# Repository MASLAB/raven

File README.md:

# raven
Robot Hardware Controller

## Pcb
Color pallet works best with KiCad wDark theme

## Firmware
Built using cmake and all dependencies exist locally

Install build tools if you need to
```
sudo apt install ninja-build cmake gcc-arm-none-eabi
```

### Compiling
Compile from motor-hub folder
```
cmake . --preset=Release
cd Release
ninja
```

### Linker Bug
For some reason, STM32CubeMX has a bug in generating the linker script, and misses RAM in a few places

Ignore the project generated linker file, as I changed the CMakeLists.txt to link to the one in firmware folder

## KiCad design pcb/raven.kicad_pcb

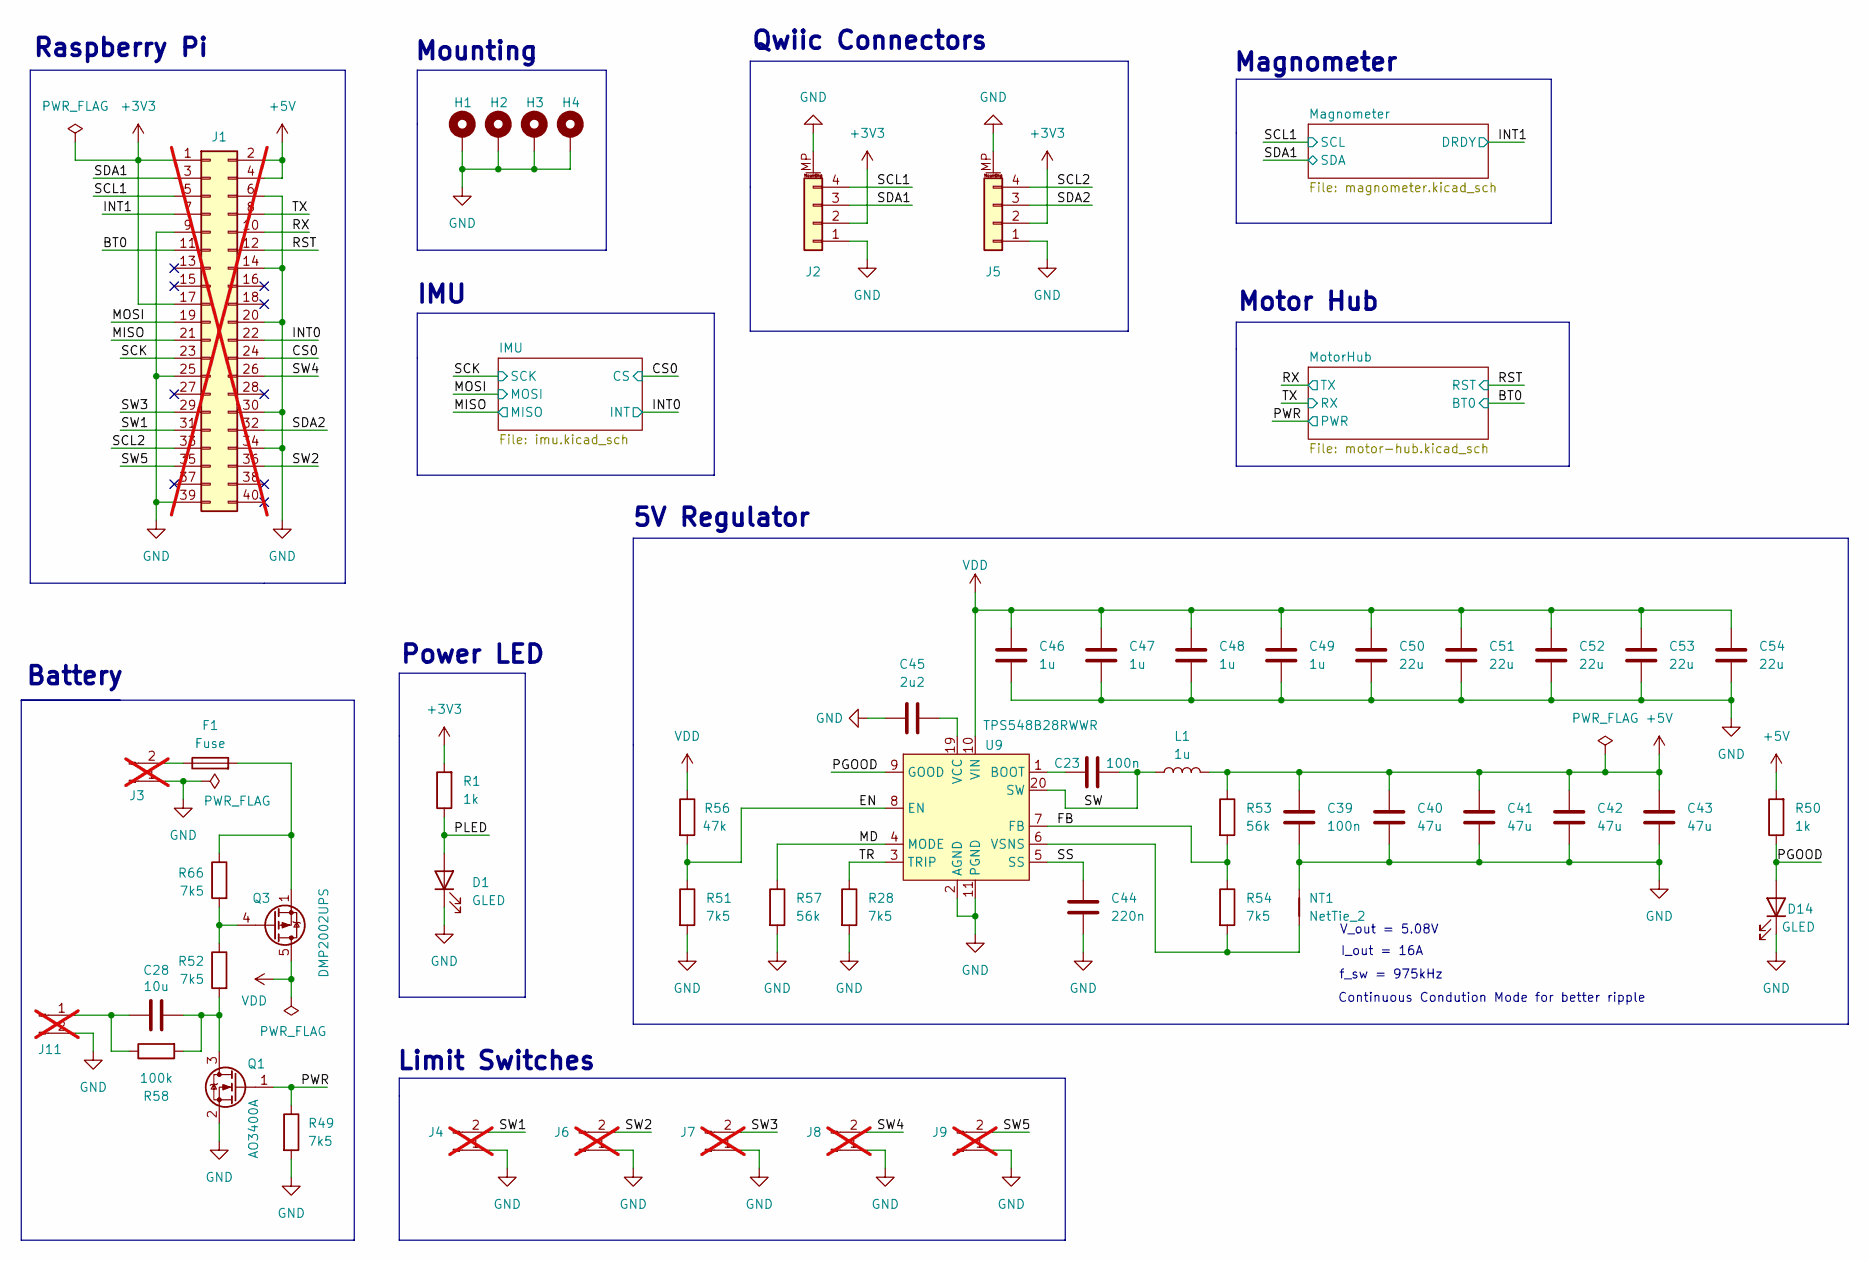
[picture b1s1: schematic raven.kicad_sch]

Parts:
C23: 100n; C_0603_1608Metric; LCSC C14663
C28: 10u; C_0603_1608Metric; LCSC C96446
C39: 100n; C_0402_1005Metric; LCSC C1525
C40, C41, C42, C43: 47u; C_1206_3216Metric; LCSC C96123
C44: 220n; C_0402_1005Metric; LCSC C16772
C45: 2u2; C_0805_2012Metric; LCSC C377773
C46, C47, C48, C49: 1u; C_0402_1005Metric; LCSC C52923
C50, C51, C52, C53, C54: 22u; C_0805_2012Metric; LCSC C45783
D1, D14: GLED; LED_0603_1608Metric; LCSC C72043
F1: Fuse; Fuse_1206_3216Metric; LCSC C2838917
H1, H2, H3, H4: MountingHole_Pad; MountingHole_2.5mm_Pad
J1: Conn_02x20_Odd_Even; PinSocket_2x20_P2.54mm_Vertical; LCSC C35165; not fitted
J2, J5: Conn_01x04_MountingPin; JST_SH_SM04B-SRSS-TB_1x04-1MP_P1.00mm_Horizontal; LCSC C160404
J3: Conn_01x02_Pin; AMASS_XT30UPB-M_1x02_P5.0mm_Vertical; LCSC C428721; not fitted
J4, J6, J7, J8, J9: Conn_01x02_Pin; PinHeader_1x02_P2.54mm_Vertical; LCSC C492401; not fitted
J11: Conn_01x02_Pin; JST_PH_B2B-PH-K_1x02_P2.00mm_Vertical; LCSC C131337; not fitted
L1: 1u; L_0660A; LCSC C18199443
NT1: NetTie_2; NetTie-2_SMD_Pad0.5mm
Q1: AO3400A; SOT-23; LCSC C20917
Q3: DMP2002UPS; LCSC C154869
R1, R50: 1k; R_0402_1005Metric; LCSC C11702
R28, R49, R51, R52, R54, R66: 7k5; R_0402_1005Metric; LCSC C25918
R53, R57: 56k; R_0402_1005Metric; LCSC C25796
R56: 47k; R_0402_1005Metric; LCSC C25792
R58: 100k; R_0402_1005Metric; LCSC C25741
U9: TPS548B28RWWR; LCSC C3188716

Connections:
+3V3: J1.1, J1.17, J2.2, J5.2, R1.2; also elsewhere on the board
+5V: C39.2, C40.1, C41.1, C42.1, C43.1, J1.2, J1.4, L1.2, R50.2, R53.1; also elsewhere on the board
/BT0: J1.11; also elsewhere on the board
/CS0: J1.24; also elsewhere on the board
/EN: R51.1, R56.2, U9.8 (EN)
/FB: R53.2, R54.1, U9.7 (FB)
/INT0: J1.22; also elsewhere on the board
/INT1: J1.7; also elsewhere on the board
/MD: R57.1, U9.4 (MODE)
/MISO: J1.21; also elsewhere on the board
/MOSI: J1.19; also elsewhere on the board
/PGOOD: D14.2 (A), R50.1, U9.9 (GOOD)
/PLED: D1.2 (A), R1.1
/PWR: Q1.1 (G), R49.1; also elsewhere on the board
/RST: J1.12; also elsewhere on the board
/RX: J1.10; also elsewhere on the board
/SCK: J1.23; also elsewhere on the board
/SCL1: J1.5, J2.4; also elsewhere on the board
/SCL2: J1.33, J5.4
/SDA1: J1.3, J2.3; also elsewhere on the board
/SDA2: J1.32, J5.3
/SS: C44.1, U9.5 (SS)
/SW: C23.2, L1.1, U9.20 (SW)
/SW1: J1.31, J4.2
/SW2: J1.36, J6.2
/SW3: J1.29, J7.2
/SW4: J1.26, J8.2
/SW5: J1.35, J9.2
/TR: R28.1, U9.3 (TRIP)
/TX: J1.8; also elsewhere on the board
GND: C39.1, C40.2, C41.2, C42.2, C43.2, C44.2, C45.1, C46.2, C47.2, C48.2, C49.2, C50.2, C51.2, C52.2, C53.2, C54.2, D1.1 (K), D14.1 (K), H1.1, H2.1, H3.1, H4.1, J1.6, J1.9, J1.14, J1.20, J1.25, J1.30, J1.34, J1.39, J2.1, J2.MP (MountPin), J3.1, J4.1, J5.1, J5.MP (MountPin), J6.1, J7.1, J8.1, J9.1, J11.2, NT1.1, Q1.2 (S), R28.2, R49.2, R51.2, R57.2, U9.2 (AGND), U9.11 (PGND), U9.12 (PGND), U9.13 (PGND), U9.14 (PGND), U9.15 (PGND), U9.16 (PGND), U9.17 (PGND), U9.18 (PGND); also elsewhere on the board
unnamed: F1.2, Q3.1 (S), Q3.2 (S), Q3.3 (S), R66.1
unnamed: F1.1, J3.2
unnamed: C28.1, J11.1, R58.1
unnamed: C28.2, Q1.3 (D), R52.2, R58.2
unnamed: Q3.4 (G), R52.1, R66.2
unnamed: C23.1, U9.1 (BOOT)
unnamed: C45.2, U9.19 (VCC)
unnamed: NT1.2, R54.2, U9.6 (VSNS)
VDD: C46.1, C47.1, C48.1, C49.1, C50.1, C51.1, C52.1, C53.1, C54.1, Q3.5 (D), Q3.6 (D), Q3.7 (D), Q3.8 (D), R56.1, U9.10 (VIN), U9.21 (VIN); also elsewhere on the board

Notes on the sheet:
Mounting
Power LED
5V Regulator
IMU
Motor Hub
V_out = 5.08V
Limit Switches
Continuous Condution Mode for better ripple
Qwiic Connectors
Battery
I_out = 16A
f_sw = 975kHz
Raspberry Pi
Magnometer

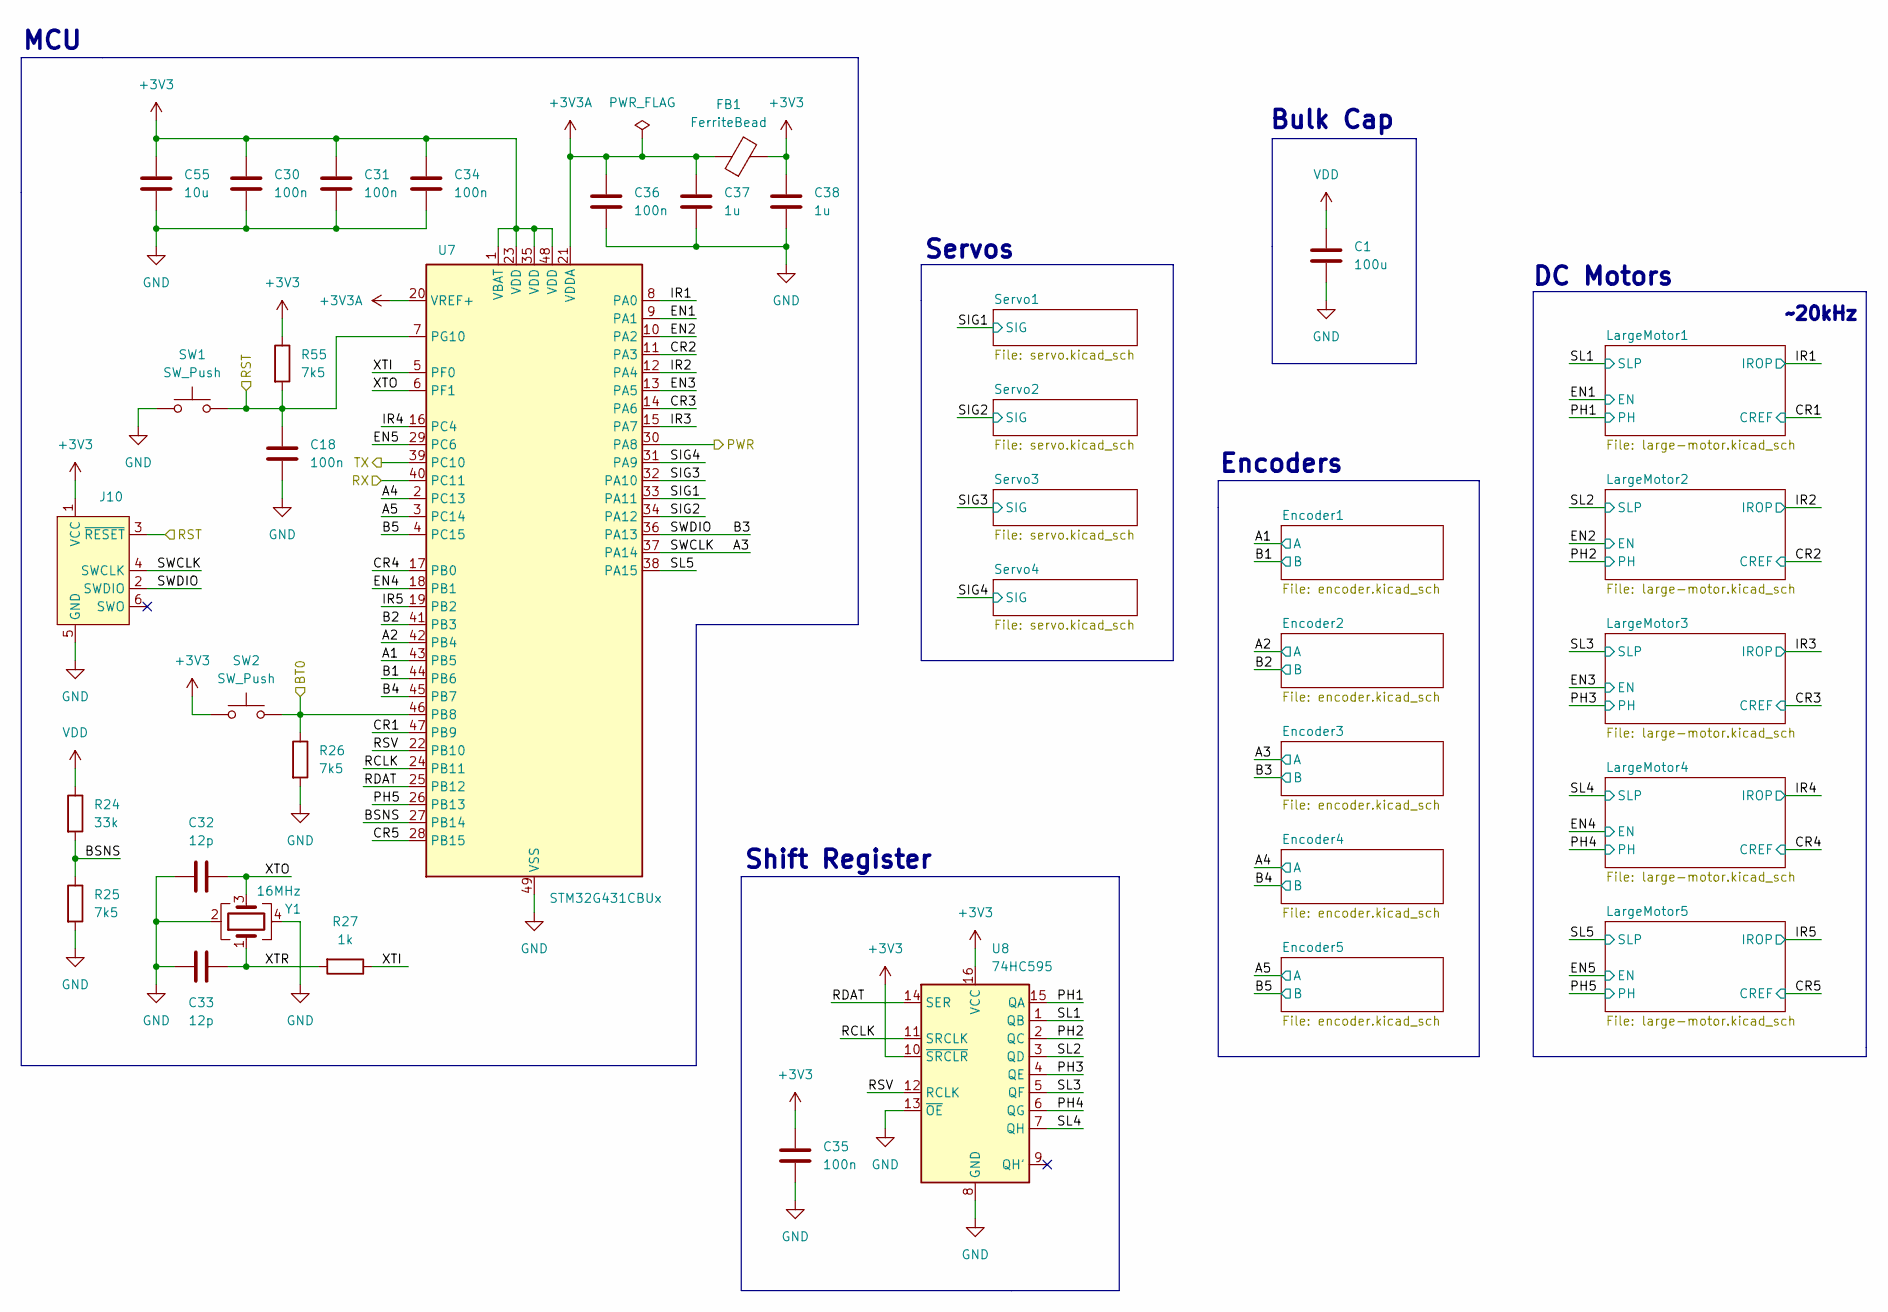
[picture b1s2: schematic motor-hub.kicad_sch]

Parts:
C1: 100u; C_Elec_8x6.2; LCSC C178539
C18, C30, C31, C34, C35, C36: 100n; C_0402_1005Metric; LCSC C1525
C32, C33: 12p; C_0402_1005Metric; LCSC C1547
C37, C38: 1u; C_0402_1005Metric; LCSC C52923
C55: 10u; C_0402_1005Metric; LCSC C15525
FB1: FerriteBead; L_0805_2012Metric; LCSC C1017
J10: Conn_ARM_SWD_TagConnect_TC2030-NL; Tag-Connect_TC2030-IDC-NL_2x03_P1.27mm_Vertical
R24: 33k; R_0402_1005Metric; LCSC C25779
R25, R26, R55: 7k5; R_0402_1005Metric; LCSC C25918
R27: 1k; R_0402_1005Metric; LCSC C11702
SW1, SW2: SW_Push; TS-1088; LCSC C720477
U7: STM32G431CBUx; QFN-48-1EP_7x7mm_P0.5mm_EP5.6x5.6mm; LCSC C529356
U8: 74HC595; SOIC-16_3.9x9.9mm_P1.27mm; LCSC C5947
Y1: 16MHz; Crystal_SMD_3225-4Pin_3.2x2.5mm; LCSC C13738

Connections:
+3V3: C30.1, C31.1, C34.1, C35.1, C38.1, C55.1, FB1.2, J10.1 (VCC), R55.1, SW2.1, U7.1 (VBAT), U7.23 (VDD), U7.35 (VDD), U7.48 (VDD), U8.10 (~SRCLR), U8.16 (VCC); also elsewhere on the board
+3V3A: C36.1, C37.1, FB1.1, U7.20 (VREF+), U7.21 (VDDA)
/BT0: R26.1, SW2.2, U7.46 (PB8); also elsewhere on the board
/MotorHub/A1: U7.43 (PB5); also elsewhere on the board
/MotorHub/A2: U7.42 (PB4); also elsewhere on the board
/MotorHub/A3: J10.4 (SWCLK), U7.37 (PA14); also elsewhere on the board
/MotorHub/A4: U7.2 (PC13); also elsewhere on the board
/MotorHub/A5: U7.3 (PC14); also elsewhere on the board
/MotorHub/B1: U7.44 (PB6); also elsewhere on the board
/MotorHub/B2: U7.41 (PB3); also elsewhere on the board
/MotorHub/B3: J10.2 (SWDIO), U7.36 (PA13); also elsewhere on the board
/MotorHub/B4: U7.45 (PB7); also elsewhere on the board
/MotorHub/B5: U7.4 (PC15); also elsewhere on the board
/MotorHub/BSNS: R24.2, R25.1, U7.27 (PB14)
/MotorHub/CR1: U7.47 (PB9); also elsewhere on the board
/MotorHub/CR2: U7.11 (PA3); also elsewhere on the board
/MotorHub/CR3: U7.14 (PA6); also elsewhere on the board
/MotorHub/CR4: U7.17 (PB0); also elsewhere on the board
/MotorHub/CR5: U7.28 (PB15); also elsewhere on the board
/MotorHub/EN1: U7.9 (PA1); also elsewhere on the board
/MotorHub/EN2: U7.10 (PA2); also elsewhere on the board
/MotorHub/EN3: U7.13 (PA5); also elsewhere on the board
/MotorHub/EN4: U7.18 (PB1); also elsewhere on the board
/MotorHub/EN5: U7.29 (PC6); also elsewhere on the board
/MotorHub/IR1: U7.8 (PA0); also elsewhere on the board
/MotorHub/IR2: U7.12 (PA4); also elsewhere on the board
/MotorHub/IR3: U7.15 (PA7); also elsewhere on the board
/MotorHub/IR4: U7.16 (PC4); also elsewhere on the board
/MotorHub/IR5: U7.19 (PB2); also elsewhere on the board
/MotorHub/PH1: U8.15 (QA); also elsewhere on the board
/MotorHub/PH2: U8.2 (QC); also elsewhere on the board
/MotorHub/PH3: U8.4 (QE); also elsewhere on the board
/MotorHub/PH4: U8.6 (QG); also elsewhere on the board
/MotorHub/PH5: U7.26 (PB13); also elsewhere on the board
/MotorHub/RCLK: U7.24 (PB11), U8.11 (SRCLK)
/MotorHub/RDAT: U7.25 (PB12), U8.14 (SER)
/MotorHub/RSV: U7.22 (PB10), U8.12 (RCLK)
/MotorHub/SIG1: U7.33 (PA11); also elsewhere on the board
/MotorHub/SIG2: U7.34 (PA12); also elsewhere on the board
/MotorHub/SIG3: U7.32 (PA10); also elsewhere on the board
/MotorHub/SIG4: U7.31 (PA9); also elsewhere on the board
/MotorHub/SL1: U8.1 (QB); also elsewhere on the board
/MotorHub/SL2: U8.3 (QD); also elsewhere on the board
/MotorHub/SL3: U8.5 (QF); also elsewhere on the board
/MotorHub/SL4: U8.7 (QH); also elsewhere on the board
/MotorHub/SL5: U7.38 (PA15); also elsewhere on the board
/MotorHub/XTI: R27.1, U7.5 (PF0)
/MotorHub/XTO: C32.2, U7.6 (PF1), Y1.3
/MotorHub/XTR: C33.2, R27.2, Y1.1
/PWR: U7.30 (PA8); also elsewhere on the board
/RST: C18.1, J10.3 (~RESET), R55.2, SW1.2, U7.7 (PG10); also elsewhere on the board
/RX: U7.39 (PC10); also elsewhere on the board
/TX: U7.40 (PC11); also elsewhere on the board
GND: C1.2, C18.2, C30.2, C31.2, C32.1, C33.1, C34.2, C35.2, C36.2, C37.2, C38.2, C55.2, J10.5 (GND), R25.2, R26.2, SW1.1, U7.49 (VSS), U8.8 (GND), U8.13 (~OE), Y1.2, Y1.4; also elsewhere on the board
VDD: C1.1, R24.1; also elsewhere on the board

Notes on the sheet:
~20kHz
Bulk Cap
Servos
MCU
DC Motors
Encoders
Shift Register

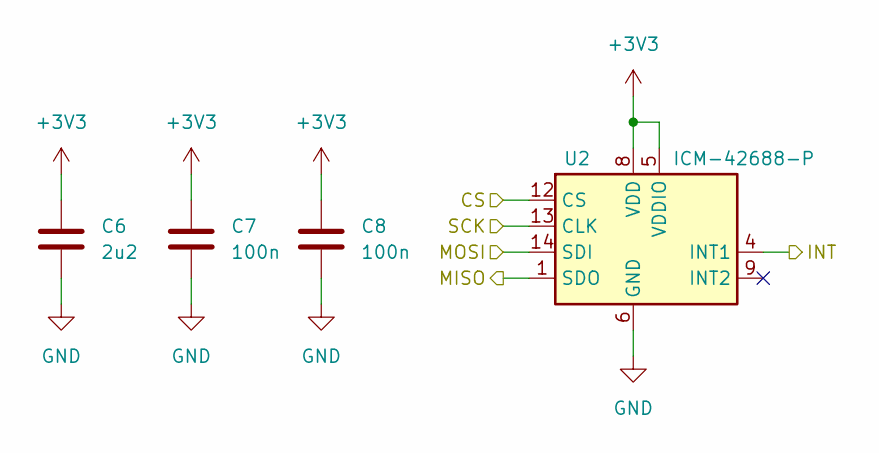
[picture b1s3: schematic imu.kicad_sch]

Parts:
C6: 2u2; C_0402_1005Metric; LCSC C12530
C7, C8: 100n; C_0402_1005Metric; LCSC C1525
U2: ICM-42688-P; LGA-14_3x2.5mm_P0.5mm_LayoutBorder3x4y; LCSC C1850418

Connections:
+3V3: C6.1, C7.1, C8.1, U2.5 (VDDIO), U2.8 (VDD); also elsewhere on the board
/CS0: U2.12 (CS); also elsewhere on the board
/INT0: U2.4 (INT1); also elsewhere on the board
/MISO: U2.1 (SDO); also elsewhere on the board
/MOSI: U2.14 (SDI); also elsewhere on the board
/SCK: U2.13 (CLK); also elsewhere on the board
GND: C6.2, C7.2, C8.2, U2.6 (GND), U2.7 (RESV), U2.11 (RESV); also elsewhere on the board

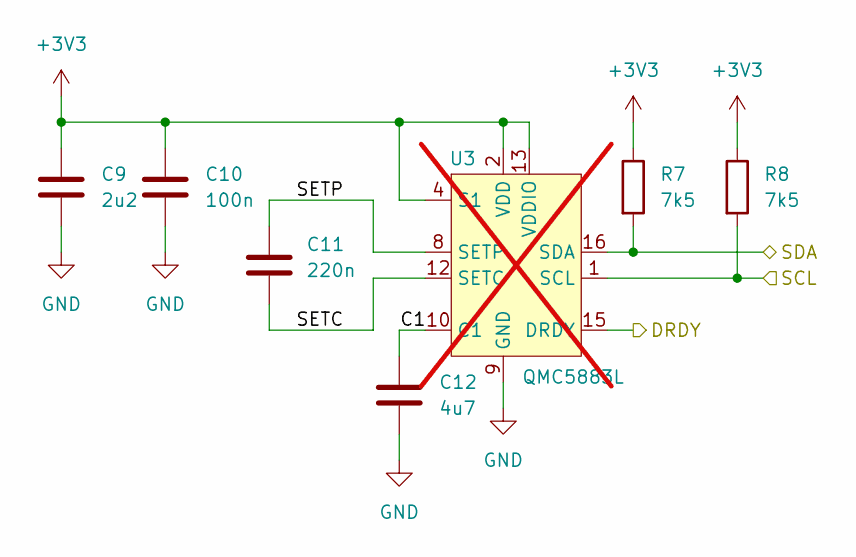
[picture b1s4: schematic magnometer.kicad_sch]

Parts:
C9: 2u2; C_0402_1005Metric; LCSC C12530
C10: 100n; C_0402_1005Metric; LCSC C1525
C11: 220n; C_0402_1005Metric; LCSC C16772
C12: 4u7; C_0603_1608Metric; LCSC C19666
R7, R8: 7k5; R_0402_1005Metric; LCSC C25918
U3: QMC5883L; LGA-16_3x3mm_P0.5mm; not fitted

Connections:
+3V3: C9.1, C10.1, R7.1, R8.1, U3.2 (VDD), U3.4 (S1), U3.13 (VDDIO); also elsewhere on the board
/INT1: U3.15 (DRDY); also elsewhere on the board
/Magnometer/C1: C12.1, U3.10 (C1)
/Magnometer/SETC: C11.2, U3.12 (SETC)
/Magnometer/SETP: C11.1, U3.8 (SETP)
/SCL1: R8.2, U3.1 (SCL); also elsewhere on the board
/SDA1: R7.2, U3.16 (SDA); also elsewhere on the board
GND: C9.2, C10.2, C12.2, U3.9 (GND), U3.11 (GND); also elsewhere on the board

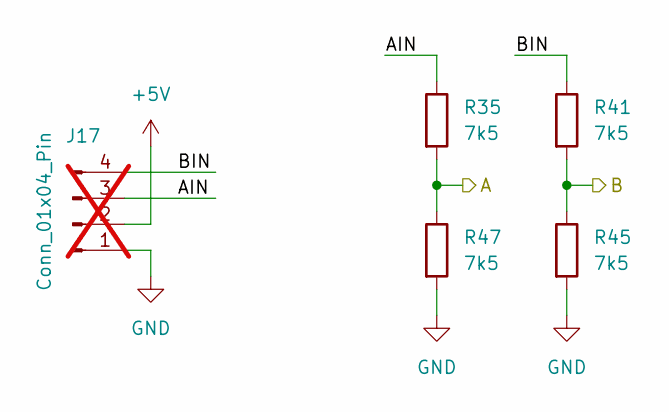
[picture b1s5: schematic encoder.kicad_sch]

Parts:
J17: Conn_01x04_Pin; PinHeader_1x04_P2.54mm_Vertical; LCSC C6332197; not fitted
R35, R41, R45, R47: 7k5; R_0402_1005Metric; LCSC C25918

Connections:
+5V: J17.2; also elsewhere on the board
/MotorHub/A4: R35.2, R47.1; also elsewhere on the board
/MotorHub/B4: R41.2, R45.1; also elsewhere on the board
/MotorHub/Encoder4/AIN: J17.3, R35.1
/MotorHub/Encoder4/BIN: J17.4, R41.1
GND: J17.1, R45.2, R47.2; also elsewhere on the board

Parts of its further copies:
J14, J15, J16, J18: Conn_01x04_Pin; PinHeader_1x04_P2.54mm_Vertical; LCSC C6332197; not fitted
R29, R30, R31, R32, R33, R34, R36, R37, R38, R39, R40, R42, R43, R44, R46, R48: 7k5; R_0402_1005Metric; LCSC C25918

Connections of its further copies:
+5V: J14.2, J15.2, J16.2, J18.2; also elsewhere on the board
/MotorHub/A1: R29.2, R30.1; also elsewhere on the board
/MotorHub/A2: R33.2, R36.1; also elsewhere on the board
/MotorHub/A3: R34.2, R42.1; also elsewhere on the board
/MotorHub/A5: R39.2, R48.1; also elsewhere on the board
/MotorHub/B1: R31.2, R32.1; also elsewhere on the board
/MotorHub/B2: R37.2, R38.1; also elsewhere on the board
/MotorHub/B3: R40.2, R44.1; also elsewhere on the board
/MotorHub/B5: R43.2, R46.1; also elsewhere on the board
/MotorHub/Encoder1/AIN: J14.3, R29.1
/MotorHub/Encoder1/BIN: J14.4, R31.1
/MotorHub/Encoder2/AIN: J15.3, R33.1
/MotorHub/Encoder2/BIN: J15.4, R37.1
/MotorHub/Encoder3/AIN: J16.3, R34.1
/MotorHub/Encoder3/BIN: J16.4, R40.1
/MotorHub/Encoder5/AIN: J18.3, R39.1
/MotorHub/Encoder5/BIN: J18.4, R43.1
GND: J14.1, J15.1, J16.1, J18.1, R30.2, R32.2, R36.2, R38.2, R42.2, R44.2, R46.2, R48.2; also elsewhere on the board

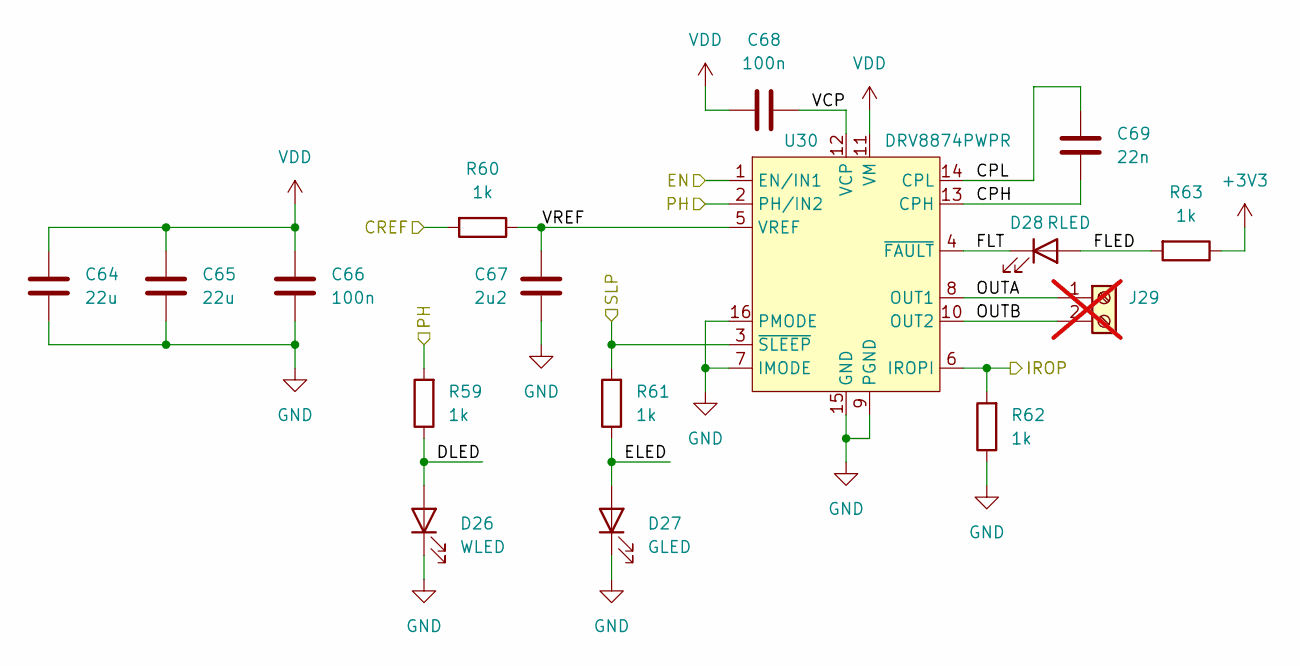
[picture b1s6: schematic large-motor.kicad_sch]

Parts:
C64, C65: 22u; C_0805_2012Metric; LCSC C45783
C66, C68: 100n; C_0402_1005Metric; LCSC C307331
C67: 2u2; C_0402_1005Metric; LCSC C12530
C69: 22n; C_0402_1005Metric; LCSC C1532
D26: WLED; LED_0603_1608Metric; LCSC C2290
D27: GLED; LED_0603_1608Metric; LCSC C72043
D28: RLED; LED_0603_1608Metric; LCSC C2286
J29: Screw_Terminal_01x02; TerminalBlock_Phoenix_MKDS-1,5-2_1x02_P5.00mm_Horizontal; LCSC C8404; not fitted
R59, R60, R61, R62, R63: 1k; R_0402_1005Metric; LCSC C11702
U30: DRV8874PWPR; HTSSOP-16-1EP_4.4x5mm_P0.65mm_EP3.4x5mm_Mask2.46x2.31mm; LCSC C1855818

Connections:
+3V3: R63.1; also elsewhere on the board
/MotorHub/CR1: R60.2; also elsewhere on the board
/MotorHub/EN1: U30.1 (EN/IN1); also elsewhere on the board
/MotorHub/IR1: R62.2, U30.6 (IROPI); also elsewhere on the board
/MotorHub/LargeMotor1/CPH: C69.2, U30.13 (CPH)
/MotorHub/LargeMotor1/CPL: C69.1, U30.14 (CPL)
/MotorHub/LargeMotor1/DLED: D26.2 (A), R59.1
/MotorHub/LargeMotor1/ELED: D27.2 (A), R61.1
/MotorHub/LargeMotor1/FLED: D28.2 (A), R63.2
/MotorHub/LargeMotor1/FLT: D28.1 (K), U30.4 (~FAULT)
/MotorHub/LargeMotor1/OUTA: J29.1, U30.8 (OUT1)
/MotorHub/LargeMotor1/OUTB: J29.2, U30.10 (OUT2)
/MotorHub/LargeMotor1/VCP: C68.2, U30.12 (VCP)
/MotorHub/LargeMotor1/VREF: C67.1, R60.1, U30.5 (VREF)
/MotorHub/PH1: R59.2, U30.2 (PH/IN2); also elsewhere on the board
/MotorHub/SL1: R61.2, U30.3 (~SLEEP); also elsewhere on the board
GND: C64.2, C65.2, C66.2, C67.2, D26.1 (K), D27.1 (K), R62.1, U30.7 (IMODE), U30.9 (PGND), U30.15 (GND), U30.16 (PMODE), U30.17 (PAD); also elsewhere on the board
VDD: C64.1, C65.1, C66.1, C68.1, U30.11 (VM); also elsewhere on the board

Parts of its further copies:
C2, C4, C14, C16, C19, C21, C24, C26: 100n; C_0402_1005Metric; LCSC C307331
C3, C15, C20, C25: 2u2; C_0402_1005Metric; LCSC C12530
C5, C17, C22, C27: 22n; C_0402_1005Metric; LCSC C1532
C13, C57, C58, C59, C60, C61, C62, C63: 22u; C_0805_2012Metric; LCSC C45783
D2, D5, D8, D11: WLED; LED_0603_1608Metric; LCSC C2290
D3, D6, D9, D12: GLED; LED_0603_1608Metric; LCSC C72043
D4, D7, D10, D13: RLED; LED_0603_1608Metric; LCSC C2286
J20, J26, J27, J28: Screw_Terminal_01x02; TerminalBlock_Phoenix_MKDS-1,5-2_1x02_P5.00mm_Horizontal; LCSC C8404; not fitted
R2, R3, R4, R5, R6, R9, R10, R11, R12, R13, R14, R15, R16, R17, R18, R19, R20, R21, R22, R23: 1k; R_0402_1005Metric; LCSC C11702
U1, U4, U5, U6: DRV8874PWPR; HTSSOP-16-1EP_4.4x5mm_P0.65mm_EP3.4x5mm_Mask2.46x2.31mm; LCSC C1855818

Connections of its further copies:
+3V3: R6.1, R13.1, R18.1, R23.1; also elsewhere on the board
/MotorHub/CR2: R3.2; also elsewhere on the board
/MotorHub/CR3: R10.2; also elsewhere on the board
/MotorHub/CR4: R15.2; also elsewhere on the board
/MotorHub/CR5: R20.2; also elsewhere on the board
/MotorHub/EN2: U1.1 (EN/IN1); also elsewhere on the board
/MotorHub/EN3: U4.1 (EN/IN1); also elsewhere on the board
/MotorHub/EN4: U5.1 (EN/IN1); also elsewhere on the board
/MotorHub/EN5: U6.1 (EN/IN1); also elsewhere on the board
/MotorHub/IR2: R5.2, U1.6 (IROPI); also elsewhere on the board
/MotorHub/IR3: R12.2, U4.6 (IROPI); also elsewhere on the board
/MotorHub/IR4: R17.2, U5.6 (IROPI); also elsewhere on the board
/MotorHub/IR5: R22.2, U6.6 (IROPI); also elsewhere on the board
/MotorHub/LargeMotor2/CPH: C5.2, U1.13 (CPH)
/MotorHub/LargeMotor2/CPL: C5.1, U1.14 (CPL)
/MotorHub/LargeMotor2/DLED: D2.2 (A), R2.1
/MotorHub/LargeMotor2/ELED: D3.2 (A), R4.1
/MotorHub/LargeMotor2/FLED: D4.2 (A), R6.2
/MotorHub/LargeMotor2/FLT: D4.1 (K), U1.4 (~FAULT)
/MotorHub/LargeMotor2/OUTA: J20.1, U1.8 (OUT1)
/MotorHub/LargeMotor2/OUTB: J20.2, U1.10 (OUT2)
/MotorHub/LargeMotor2/VCP: C4.2, U1.12 (VCP)
/MotorHub/LargeMotor2/VREF: C3.1, R3.1, U1.5 (VREF)
/MotorHub/LargeMotor3/CPH: C17.2, U4.13 (CPH)
/MotorHub/LargeMotor3/CPL: C17.1, U4.14 (CPL)
/MotorHub/LargeMotor3/DLED: D5.2 (A), R9.1
/MotorHub/LargeMotor3/ELED: D6.2 (A), R11.1
/MotorHub/LargeMotor3/FLED: D7.2 (A), R13.2
/MotorHub/LargeMotor3/FLT: D7.1 (K), U4.4 (~FAULT)
/MotorHub/LargeMotor3/OUTA: J26.1, U4.8 (OUT1)
/MotorHub/LargeMotor3/OUTB: J26.2, U4.10 (OUT2)
/MotorHub/LargeMotor3/VCP: C16.2, U4.12 (VCP)
/MotorHub/LargeMotor3/VREF: C15.1, R10.1, U4.5 (VREF)
/MotorHub/LargeMotor4/CPH: C22.2, U5.13 (CPH)
/MotorHub/LargeMotor4/CPL: C22.1, U5.14 (CPL)
/MotorHub/LargeMotor4/DLED: D8.2 (A), R14.1
/MotorHub/LargeMotor4/ELED: D9.2 (A), R16.1
/MotorHub/LargeMotor4/FLED: D10.2 (A), R18.2
/MotorHub/LargeMotor4/FLT: D10.1 (K), U5.4 (~FAULT)
/MotorHub/LargeMotor4/OUTA: J27.1, U5.8 (OUT1)
/MotorHub/LargeMotor4/OUTB: J27.2, U5.10 (OUT2)
/MotorHub/LargeMotor4/VCP: C21.2, U5.12 (VCP)
/MotorHub/LargeMotor4/VREF: C20.1, R15.1, U5.5 (VREF)
/MotorHub/LargeMotor5/CPH: C27.2, U6.13 (CPH)
/MotorHub/LargeMotor5/CPL: C27.1, U6.14 (CPL)
/MotorHub/LargeMotor5/DLED: D11.2 (A), R19.1
/MotorHub/LargeMotor5/ELED: D12.2 (A), R21.1
/MotorHub/LargeMotor5/FLED: D13.2 (A), R23.2
/MotorHub/LargeMotor5/FLT: D13.1 (K), U6.4 (~FAULT)
/MotorHub/LargeMotor5/OUTA: J28.1, U6.8 (OUT1)
/MotorHub/LargeMotor5/OUTB: J28.2, U6.10 (OUT2)
/MotorHub/LargeMotor5/VCP: C26.2, U6.12 (VCP)
/MotorHub/LargeMotor5/VREF: C25.1, R20.1, U6.5 (VREF)
/MotorHub/PH2: R2.2, U1.2 (PH/IN2); also elsewhere on the board
/MotorHub/PH3: R9.2, U4.2 (PH/IN2); also elsewhere on the board
/MotorHub/PH4: R14.2, U5.2 (PH/IN2); also elsewhere on the board
/MotorHub/PH5: R19.2, U6.2 (PH/IN2); also elsewhere on the board
/MotorHub/SL2: R4.2, U1.3 (~SLEEP); also elsewhere on the board
/MotorHub/SL3: R11.2, U4.3 (~SLEEP); also elsewhere on the board
/MotorHub/SL4: R16.2, U5.3 (~SLEEP); also elsewhere on the board
/MotorHub/SL5: R21.2, U6.3 (~SLEEP); also elsewhere on the board
GND: C2.2, C3.2, C13.2, C14.2, C15.2, C19.2, C20.2, C24.2, C25.2, C57.2, C58.2, C59.2, C60.2, C61.2, C62.2, C63.2, D2.1 (K), D3.1 (K), D5.1 (K), D6.1 (K), D8.1 (K), D9.1 (K), D11.1 (K), D12.1 (K), R5.1, R12.1, R17.1, R22.1, U1.7 (IMODE), U1.9 (PGND), U1.15 (GND), U1.16 (PMODE), U1.17 (PAD), U4.7 (IMODE), U4.9 (PGND), U4.15 (GND), U4.16 (PMODE), U4.17 (PAD), U5.7 (IMODE), U5.9 (PGND), U5.15 (GND), U5.16 (PMODE), U5.17 (PAD), U6.7 (IMODE), U6.9 (PGND), U6.15 (GND), U6.16 (PMODE), U6.17 (PAD); also elsewhere on the board
VDD: C2.1, C4.1, C13.1, C14.1, C16.1, C19.1, C21.1, C24.1, C26.1, C57.1, C58.1, C59.1, C60.1, C61.1, C62.1, C63.1, U1.11 (VM), U4.11 (VM), U5.11 (VM), U6.11 (VM); also elsewhere on the board

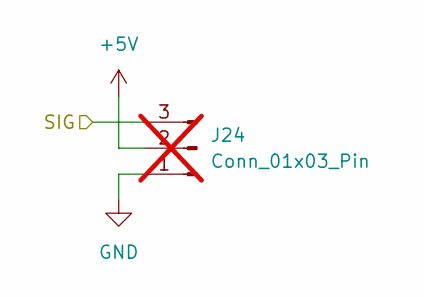
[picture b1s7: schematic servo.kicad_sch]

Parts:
J24: Conn_01x03_Pin; PinHeader_1x03_P2.54mm_Vertical; LCSC C6332196; not fitted

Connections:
+5V: J24.2; also elsewhere on the board
/MotorHub/SIG4: J24.3; also elsewhere on the board
GND: J24.1; also elsewhere on the board

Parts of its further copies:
J21, J22, J23: Conn_01x03_Pin; PinHeader_1x03_P2.54mm_Vertical; LCSC C6332196; not fitted

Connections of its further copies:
+5V: J21.2, J22.2, J23.2; also elsewhere on the board
/MotorHub/SIG1: J21.3; also elsewhere on the board
/MotorHub/SIG2: J22.3; also elsewhere on the board
/MotorHub/SIG3: J23.3; also elsewhere on the board
GND: J21.1, J22.1, J23.1; also elsewhere on the board

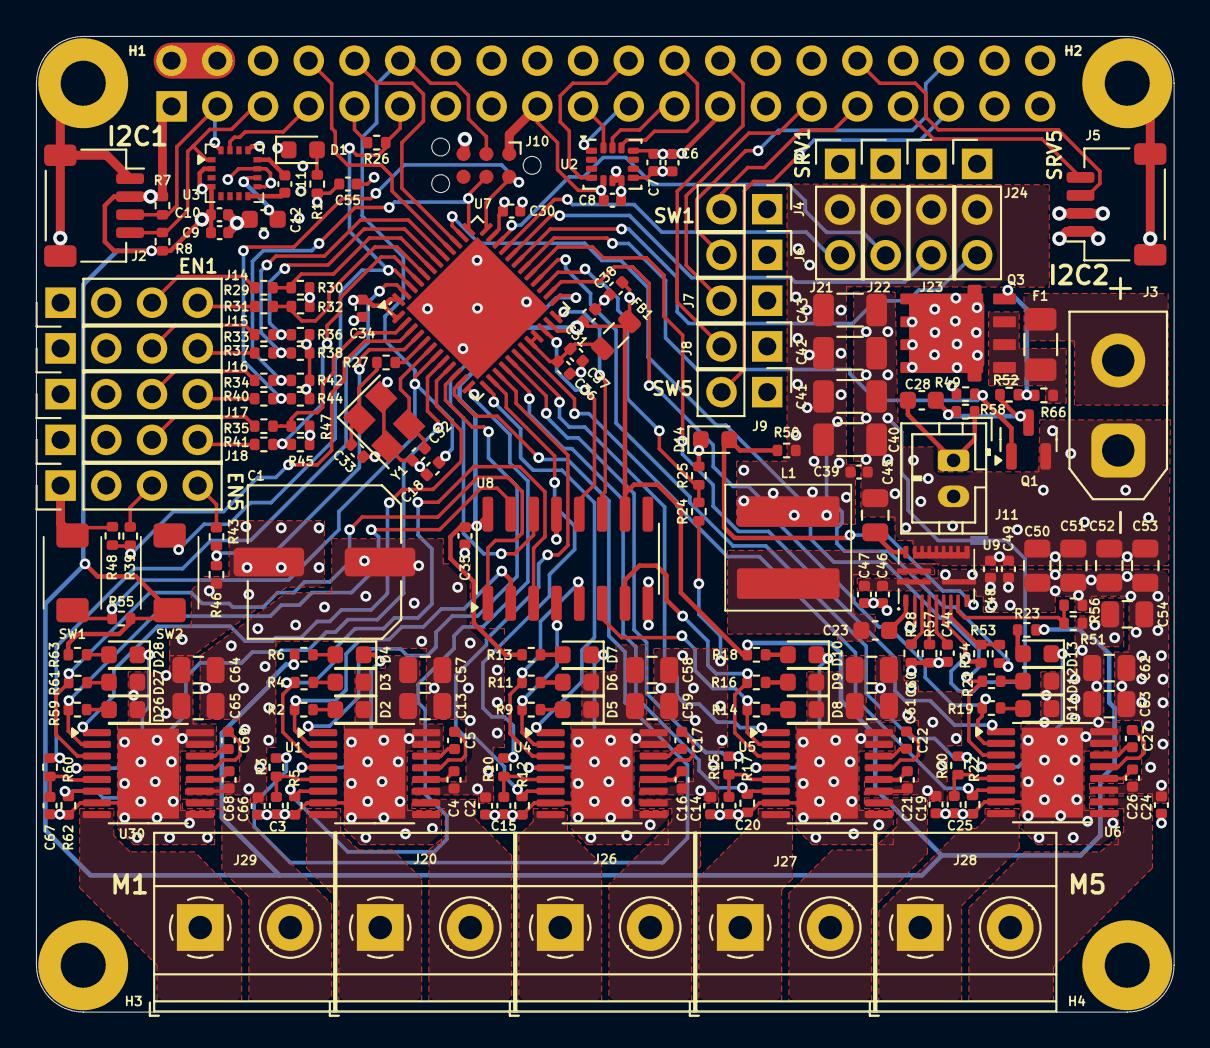
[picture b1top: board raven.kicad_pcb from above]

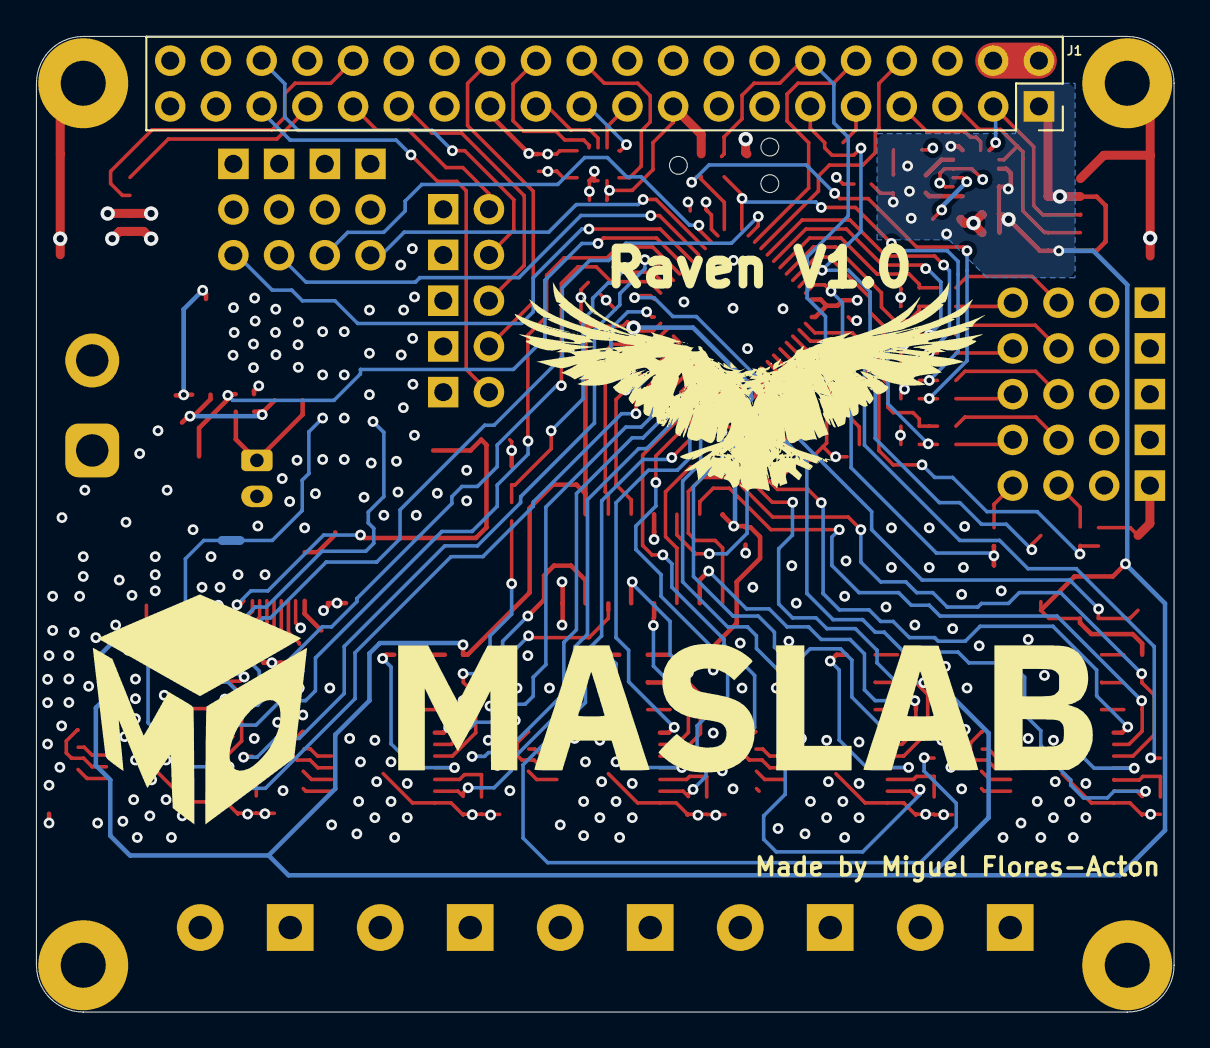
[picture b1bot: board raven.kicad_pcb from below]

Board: 4 copper layers, 63.2 x 54.2 mm, 198 parts (4 on the bottom side), 150 nets.

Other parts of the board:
G1, G2: LOGO

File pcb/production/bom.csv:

Designator,Footprint,Quantity,Value,LCSC Part #
C1,C_Elec_8x6.2,1,100u,C178539
"C10, C18, C30, C31, C34, C35, C36, C39, C7, C8",0402,10,100n,C1525
"C11, C44",0402,2,220n,C16772
C12,0603,1,4u7,C19666
"C13, C50, C51, C52, C53, C54, C57, C58, C59, C60, C61, C62, C63, C64, C65",0805,15,22u,C45783
"C14, C16, C19, C2, C21, C24, C26, C4, C66, C68",0402,10,100n,C307331
"C15, C20, C25, C3, C6, C67, C9",0402,7,2u2,C12530
"C17, C22, C27, C5, C69",0402,5,22n,C1532
C23,0603,1,100n,C14663
C28,0603,1,10u,C96446
"C32, C33",0402,2,12p,C1547
"C37, C38, C46, C47, C48, C49",0402,6,1u,C52923
"C40, C41, C42, C43",1206,4,47u,C96123
C45,0805,1,2u2,C377773
C55,0402,1,10u,C15525
"D1, D12, D14, D27, D3, D6, D9",0603,7,GLED,C72043
"D10, D13, D28, D4, D7",0603,5,RLED,C2286
"D11, D2, D26, D5, D8",0603,5,WLED,C2290
F1,1206,1,Fuse,C2838917
FB1,0805,1,FerriteBead,C1017
"J2, J5",JST_SH_SM04B-SRSS-TB_1x04-1MP_P1.00mm_Horizontal,2,Conn_01x04_MountingPin,C160404
L1,L_0660A,1,1u,C18199443
Q1,SOT-23,1,AO3400A,C20917
Q3,DMP2002UPS,1,DMP2002UPS,C154869
"R1, R10, R11, R12, R13, R14, R15, R16, R17, R18, R19, R2, R20, R21, R22, R23, R27, R3, R4, R5, R50, R59, R6, R60, R61, R62, R63, R9",0402,28,1k,C11702
R24,0402,1,33k,C25779
"R25, R26, R28, R29, R30, R31, R32, R33, R34, R35, R36, R37, R38, R39, R40, R41, R42, R43, R44, R45, R46, R47, R48, R49, R51, R52, R54, R55, R66, R7, R8",0402,31,7k5,C25918
"R53, R57",0402,2,56k,C25796
R56,0402,1,47k,C25792
R58,0402,1,100k,C25741
"SW1, SW2",TS-1088,2,SW_Push,C720477
"U1, U30, U4, U5, U6",HTSSOP-16-1EP_4.4x5mm_P0.65mm_EP3.4x5mm_Mask2.46x2.31mm,5,DRV8874PWPR,C1855818
U2,LGA-14_3x2.5mm_P0.5mm_LayoutBorder3x4y,1,ICM-42688-P,C1850418
U7,QFN-48-1EP_7x7mm_P0.5mm_EP5.6x5.6mm,1,STM32G431CBUx,C529356
U8,SOIC-16_3.9x9.9mm_P1.27mm,1,74HC595,C5947
U9,TPS548B28RWWR,1,TPS548B28RWWR,C3188716
Y1,Crystal_SMD_3225-4Pin_3.2x2.5mm,1,16MHz,C13738

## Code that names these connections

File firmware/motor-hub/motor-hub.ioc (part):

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Mcu.Name=STM32G431C(6-8-B)Ux
Mcu.Package=UFQFPN48
Mcu.UserName=STM32G431CBUx
PA0.Mode=IN1-Single-Ended
PA0.Signal=ADC1_IN1
PA1.Signal=S_TIM2_CH2
PA10.Signal=S_TIM1_CH3
PA11.Signal=S_TIM1_CH4
PA12.Signal=S_TIM16_CH1
PA13.GPIOParameters=GPIO_Label
PA13.GPIO_Label=B3
PA13.Signal=GPIO_Input
PA14.GPIOParameters=GPIO_Label
PA14.GPIO_Label=A3
PA14.Signal=GPIO_Input
PA15.GPIOParameters=GPIO_Label
PA15.GPIO_Label=SL5
PA15.Signal=GPIO_Output
PA2.Signal=S_TIM2_CH3
PA3.Signal=S_TIM2_CH4
PA4.Mode=IN17-Single-Ended
PA4.Signal=ADC2_IN17
PA5.Signal=S_TIM2_CH1
PA6.Signal=S_TIM3_CH1
PA7.Mode=IN4-Single-Ended
PA7.Signal=ADC2_IN4
PA8.GPIOParameters=PinState,GPIO_Label
PA8.GPIO_Label=PWR
PA8.PinState=GPIO_PIN_SET
PA8.Signal=GPIO_Output
PA9.Signal=S_TIM1_CH2
PB0.Signal=S_TIM3_CH3
PB1.Signal=S_TIM3_CH4
PB10.GPIOParameters=GPIO_Label
PB10.GPIO_Label=RSV
PB10.Signal=GPIO_Output
PB11.GPIOParameters=GPIO_Label
PB11.GPIO_Label=RCLK
PB11.Signal=GPIO_Output
PB12.GPIOParameters=GPIO_Label
PB12.GPIO_Label=RDAT
PB12.Signal=GPIO_Output
PB13.GPIOParameters=GPIO_Label
PB13.GPIO_Label=PH5
PB13.Signal=GPIO_Output
PB14.Mode=IN5-Single-Ended
PB14.Signal=ADC1_IN5
PB15.Signal=S_TIM15_CH2
PB2.Mode=IN12-Single-Ended
PB2.Signal=ADC2_IN12
PB3.GPIOParameters=GPIO_Label
PB3.GPIO_Label=B2
PB3.Signal=GPIO_Input
PB4.GPIOParameters=GPIO_Label
PB4.GPIO_Label=A2
PB4.Signal=GPIO_Input
PB5.GPIOParameters=GPIO_Label
PB5.GPIO_Label=A1
PB5.Signal=GPIO_Input
PB6.GPIOParameters=GPIO_Label
PB6.GPIO_Label=B1
PB6.Signal=GPIO_Input
PB7.GPIOParameters=GPIO_Label
PB7.GPIO_Label=B4
PB7.Signal=GPIO_Input
PB9.Signal=S_TIM4_CH4
PC10.Mode=Asynchronous
PC10.Signal=USART3_TX
PC11.Mode=Asynchronous
PC11.Signal=USART3_RX
PC13.GPIOParameters=GPIO_Label
PC13.GPIO_Label=A4
PC13.Signal=GPIO_Input
PC14-OSC32_IN.GPIOParameters=GPIO_Label
PC14-OSC32_IN.GPIO_Label=A5
PC14-OSC32_IN.Signal=GPIO_Input
PC15-OSC32_OUT.GPIOParameters=GPIO_Label
PC15-OSC32_OUT.GPIO_Label=B5
PC15-OSC32_OUT.Signal=GPIO_Input
PC4.Mode=IN5-Single-Ended
PC4.Signal=ADC2_IN5
PC6.Signal=S_TIM8_CH1
PF0-OSC_IN.Mode=HSE-External-Oscillator
PF0-OSC_IN.Signal=RCC_OSC_IN
PF1-OSC_OUT.Mode=HSE-External-Oscillator
PF1-OSC_OUT.Signal=RCC_OSC_OUT
RCC.HSE_VALUE=16000000
RCC.SYSCLKFreq_VALUE=168000000
RCC.SYSCLKSource=RCC_SYSCLKSOURCE_PLLCLK
board=custom
